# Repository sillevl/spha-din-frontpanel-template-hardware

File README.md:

# Front-panel template

Reusable KiCad design used as the basis for SPHA module front panels.

> **Lifecycle: retain as a template or historical design.** Its schematic is shared with an input front panel, but its PCB, project settings, and final backup are unique; outright removal is not currently valid. See `../../docs/hardware-project-lifecycle-review.md`.

## Design files

- `frontpanel-template.kicad_pro` — KiCad project
- `frontpanel-template.kicad_sch` — top-level schematic
- `frontpanel-template.kicad_pcb` — PCB layout

## Working with the project

Open the `.kicad_pro` file in KiCad. The design includes files originating from an older KiCad workflow; review schematic links, footprints, design rules, zones, and manufacturing outputs after any conversion or upgrade.

KiCad source files and project-specific libraries are the source of truth. Generated BOM, Gerber, assembly, and fabrication-house outputs are excluded from the repository; regenerate and verify them before manufacturing.

## Repository notes

Temporary KiCad state, locks, autosaves, and backup directories are excluded by `.gitignore`. Board revision, tested KiCad version, manufacturing revision, and hardware/firmware compatibility still need to be recorded when provenance is confirmed.

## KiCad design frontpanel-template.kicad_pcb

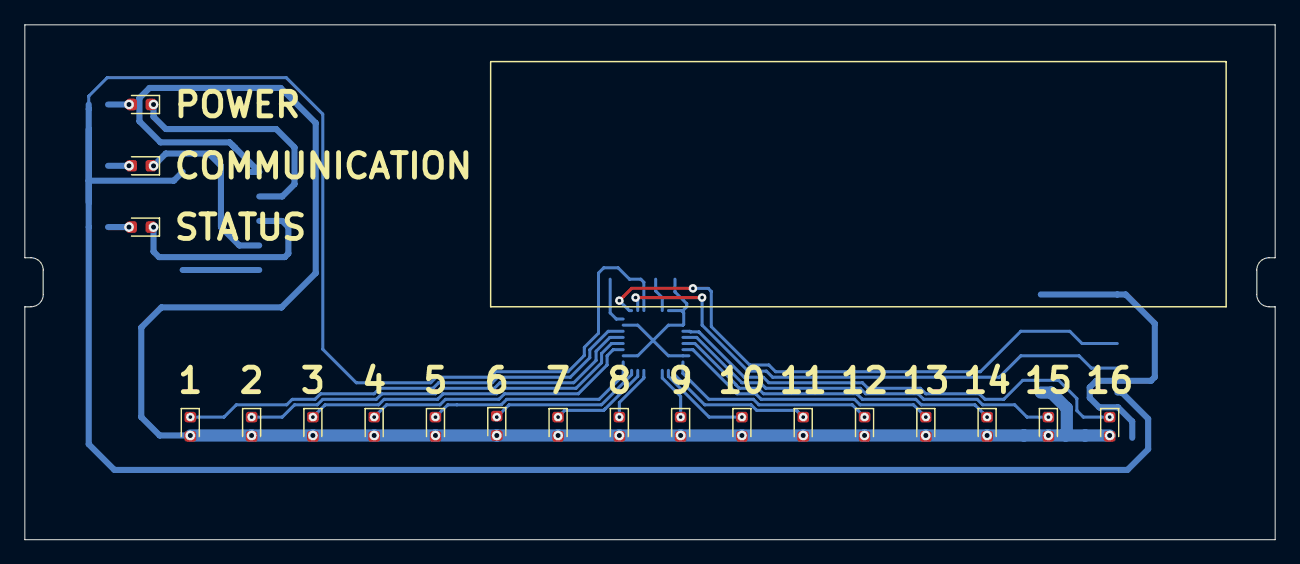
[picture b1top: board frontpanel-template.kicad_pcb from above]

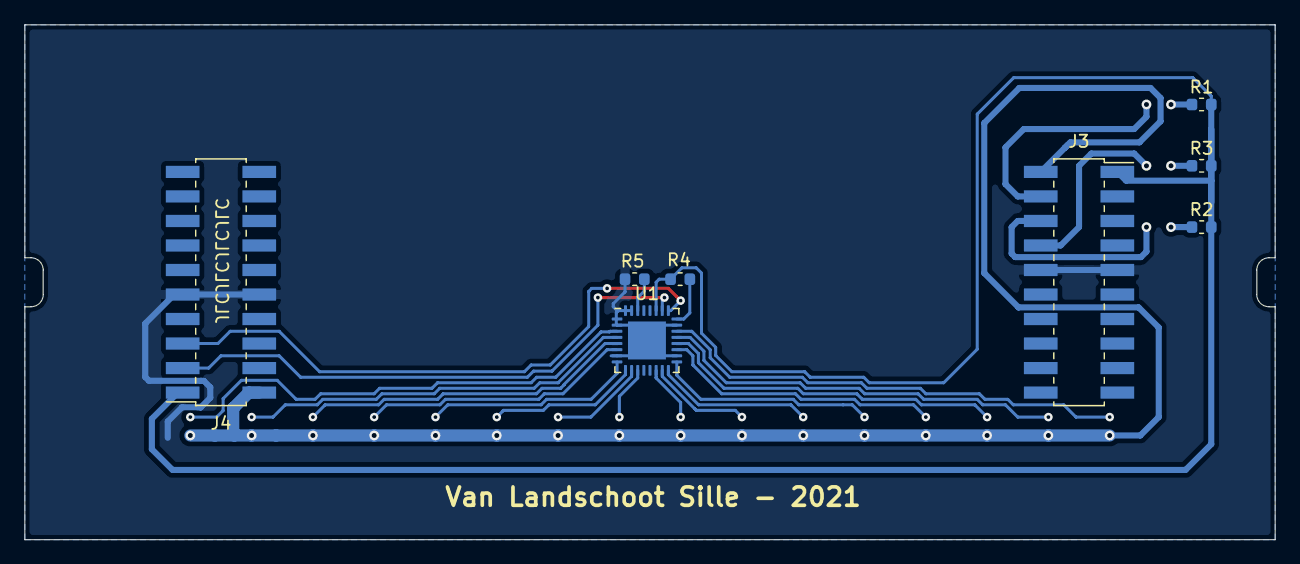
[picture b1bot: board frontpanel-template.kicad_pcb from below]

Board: 2 copper layers, 102.0 x 42.0 mm, 27 parts (8 on the bottom side), 29 nets.

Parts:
D1: POWER; LED_0603_1608Metric
D2: STATUS; LED_0603_1608Metric
D3: COMMUNICATION; LED_0603_1608Metric
D4: 1; LED_0603_1608Metric
D5: 2; LED_0603_1608Metric
D6: 3; LED_0603_1608Metric
D7: 4; LED_0603_1608Metric
D8: 5; LED_0603_1608Metric
D9: 6; LED_0603_1608Metric
D10: 7; LED_0603_1608Metric
D11: 8; LED_0603_1608Metric
D12: 9; LED_0603_1608Metric
D13: 10; LED_0603_1608Metric
D14: 11; LED_0603_1608Metric
D15: 12; LED_0603_1608Metric
D16: 13; LED_0603_1608Metric
D17: 14; LED_0603_1608Metric
D18: 15; LED_0603_1608Metric
D19: 16; LED_0603_1608Metric
J3, J4: Conn_02x10_Odd_Even; PinSocket_2x10_P2.00mm_Vertical_SMD
R1, R2, R3, R4, R5: 1K; R_0603_1608Metric
U1: TLC59116; VQFN-32-1EP_5x5mm_P0.5mm_EP3.1x3.1mm

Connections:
+3V3: J3.1, J4.1, R1.2, R2.2, R3.2, R4.2, U1.27 (VDD)
+5V: D4.2 (A), D5.2 (A), D6.2 (A), D7.2 (A), D8.2 (A), D9.2 (A), D10.2 (A), D11.2 (A), D12.2 (A), D13.2 (A), D14.2 (A), D15.2 (A), D16.2 (A), D17.2 (A), D18.2 (A), D19.2 (A), J3.2, J4.2
/LED-COMM-1: D3.1 (K), J3.8
/LED-POWER-1: D1.1 (K), J3.4
/LED-STATUS-1: D2.1 (K), J3.6
/SCL-2: J4.5, U1.25 (SCL)
/SDA-2: J4.3, U1.26 (SDA)
GND: J3.9, J3.10, J4.9, J4.10, R5.2, U1.1 (A2), U1.2 (A3), U1.7 (GND), U1.18 (GND), U1.23 (GND), U1.31 (A0), U1.32 (A1), U1.33
unnamed: D1.2 (A), R1.1
unnamed: D2.2 (A), R2.1
unnamed: D3.2 (A), R3.1
unnamed: D4.1 (K), U1.22 (OUT15)
unnamed: D5.1 (K), U1.21 (OUT14)
unnamed: D6.1 (K), U1.20 (OUT13)
unnamed: D7.1 (K), U1.19 (OUT12)
unnamed: D8.1 (K), U1.17 (OUT11)
unnamed: D9.1 (K), U1.16 (OUT10)
unnamed: D10.1 (K), U1.15 (OUT9)
unnamed: D11.1 (K), U1.14 (OUT8)
unnamed: D12.1 (K), U1.11 (OUT7)
unnamed: D13.1 (K), U1.10 (OUT6)
unnamed: D14.1 (K), U1.9 (OUT5)
unnamed: D15.1 (K), U1.8 (OUT4)
unnamed: D16.1 (K), U1.6 (OUT3)
unnamed: D17.1 (K), U1.5 (OUT2)
unnamed: D18.1 (K), U1.4 (OUT1)
unnamed: D19.1 (K), U1.3 (OUT0)
unnamed: R4.1, U1.24 (RESET)
unnamed: R5.1, U1.30 (REXT)
